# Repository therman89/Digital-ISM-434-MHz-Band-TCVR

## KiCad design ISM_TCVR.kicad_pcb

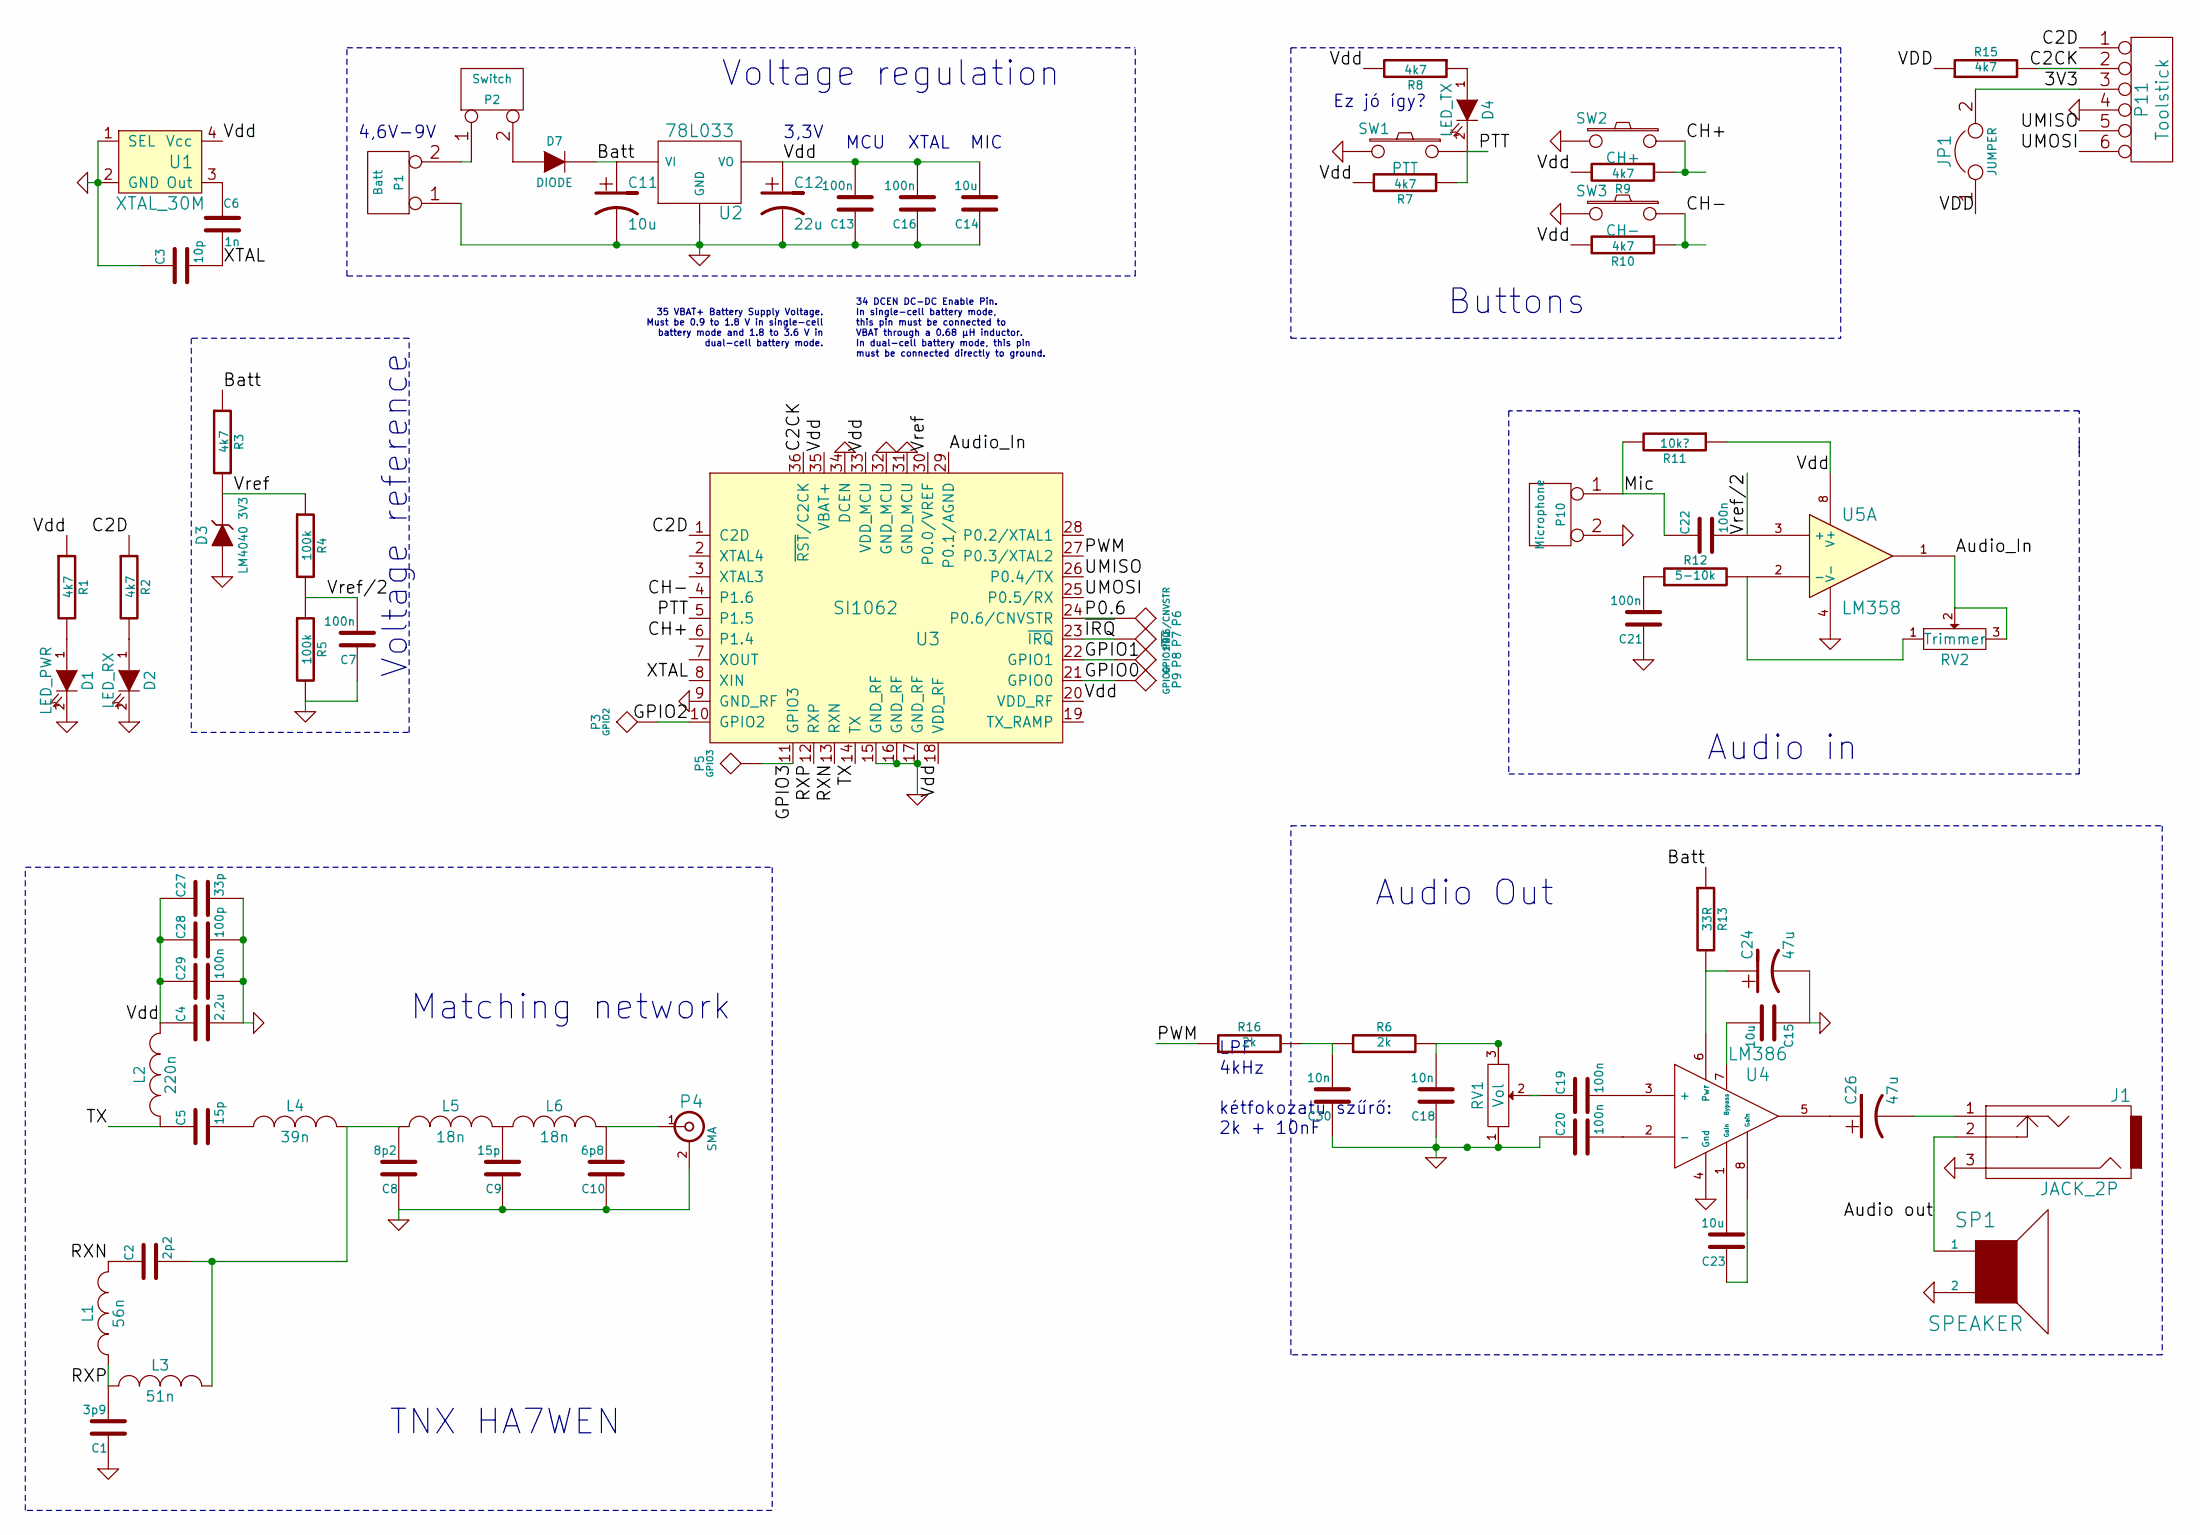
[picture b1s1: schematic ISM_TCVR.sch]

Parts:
C1: 3p9
C2: 2p2
C3: 10p
C4: 2,2u
C5, C9: 15p
C6: 1n
C7, C13, C16, C19, C20, C21, C22, C29: 100n
C8: 8p2
C10: 6p8
C11, C14, C15, C23: 10u
C12: 22u
C18, C30: 10n
C24, C26: 47u
C27: 33p
C28: 100p
D1: LED_PWR
D2: LED_RX
D3: LM4040 3V3
D4: LED_TX
D7: DIODE
J1: JACK_2P
JP1: JUMPER
L1: 56n
L2: 220n
L3: 51n
L4: 39n
L5, L6: 18n
P1: Batt
P2: Switch
P3: GPIO2
P4: SMA
P5: GPIO3
P6: P0.6/CNVSTR
P7: ~IRQ
P8: GPIO1
P9: GPIO0
P10: Microphone
P11: Toolstick
R1, R2, R3, R7, R8, R9, R10, R15: 4k7
R4, R5: 100k
R6, R16: 2k
R11: 10k?
R12: 5-10k
R13: 33R
RV1: Vol
RV2: Trimmer
SP1: SPEAKER
SW1: PTT
SW2: CH+
SW3: CH-
U1: XTAL_30M
U2: 78L033
U3: SI1062
U4: LM386
U5: LM358

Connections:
/3V3: JP1.2, P11.3
/Audio out: J1.2, SP1.1
/Audio_In: RV2.2, RV2.3, U3.29 (P0.1/AGND), U5.1
/Batt: C11.1, D7.2 (K), R3.1, R13.1, U2.3 (VI)
/C2CK: P11.2, R15.2, U3.36 (~RST~/C2CK)
/C2D: P11.1, R2.1, U3.1 (C2D)
/CH+: R9.1, SW2.1, U3.6 (P1.4)
/CH-: R10.1, SW3.1, U3.4 (P1.6)
/GPIO0: P9.1, U3.21 (GPIO0)
/GPIO1: P8.1, U3.22 (GPIO1)
/GPIO2: P3.1, U3.10 (GPIO2)
/GPIO3: P5.1, U3.11 (GPIO3)
/Mic: C22.1, P10.1, R11.2
/P0.6: P6.1, U3.24 (P0.6/CNVSTR)
/PTT: D4.2 (K), R7.1, SW1.1, U3.5 (P1.5)
/PWM: R16.1, U3.27 (P0.3/XTAL2)
/RXN: C2.1, L1.2, U3.13 (RXN)
/RXP: C1.2, L1.1, L3.1, U3.12 (RXP)
/TX: C5.1, L2.1, U3.14 (TX)
/UMISO: P11.5, U3.26 (P0.4/TX)
/UMOSI: P11.6, U3.25 (P0.5/RX)
/VDD: C4.1, C12.1, C13.2, C14.2, C16.2, C27.1, C28.1, C29.1, JP1.1, L2.2, R1.1, R7.2, R8.2, R9.2, R10.2, R11.1, R15.1, U1.4 (Vcc), U2.2 (VO), U3.18 (VDD_RF), U3.20 (VDD_RF), U3.33 (VDD_MCU), U3.35 (VBAT+), U5.8 (V+)
/Vref: D3.1 (K), R3.2, R4.1, U3.30 (P0.0/VREF)
/Vref/2: C7.2, C22.2, R4.2, R5.1, U5.3 (+)
/XTAL: C3.2, C6.2, U3.8 (XIN)
/~IRQ: P7.1, U3.23 (~IRQ)
GND: C1.1, C3.1, C4.2, C7.1, C8.1, C9.1, C10.1, C11.2, C12.2, C13.1, C14.1, C15.1, C16.1, C18.1, C20.1, C21.1, C24.2, C27.2, C28.2, C29.2, C30.1, D1.2 (K), D2.2 (K), D3.2 (A), J1.3, P1.1, P4.2 (Ext), P10.2 (PM), P11.4, R5.2, RV1.1, SP1.2, SW1.2, SW2.2, SW3.2, U1.1 (SEL), U1.2 (GND), U2.1 (GND), U3.9 (GND_RF), U3.15 (GND_RF), U3.16 (GND_RF), U3.17 (GND_RF), U3.31 (GND_MCU), U3.32 (GND_MCU), U3.34 (DCEN), U4.4 (Gnd), U5.4 (V-)
unnamed: C23.1, U4.8 (Gain)
unnamed: C18.2, R6.2, RV1.3
unnamed: C26.2, J1.1
unnamed: C2.2, C8.2, L3.2, L4.2, L5.1
unnamed: C10.2, L6.2, P4.1 (In)
unnamed: D7.1 (A), P2.2 (PM)
unnamed: P1.2 (PM), P2.1
unnamed: C21.2, R12.1
unnamed: C15.2, U4.7 (Bypass)
unnamed: C6.1, U1.3 (Out)
unnamed: C30.2, R6.1, R16.2
unnamed: C24.1, R13.2, U4.6 (Pwr)
unnamed: C19.1, RV1.2
unnamed: R12.2, RV2.1, U5.2 (-)
unnamed: C23.2, U4.1 (Gain)
unnamed: C26.1, U4.5
unnamed: C19.2, U4.3 (+)
unnamed: C20.2, U4.2 (-)
unnamed: C9.2, L5.2, L6.1
unnamed: C5.2, L4.1
unnamed: D1.1 (A), R1.2
unnamed: D2.1 (A), R2.2
unnamed: D4.1 (A), R8.1

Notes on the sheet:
Matching network
LPF 4kHz kétfokozatú szűrő: 2k + 10nF
3,3V
MCU
MIC
4,6V-9V
34 DCEN DC-DC Enable Pin. In single-cell battery mode, this pin must be connected to VBAT through a 0.68 μH inductor. In dual-cell battery mode, this pin must be connected directly to ground.
35 VBAT+ Battery Supply Voltage. Must be 0.9 to 1.8 V in single-cell battery mode and 1.8 to 3.6 V in dual-cell battery mode.
Audio in
Audio Out
Voltage regulation
TNX HA7WEN
Voltage reference
XTAL
Buttons
Ez jó így?

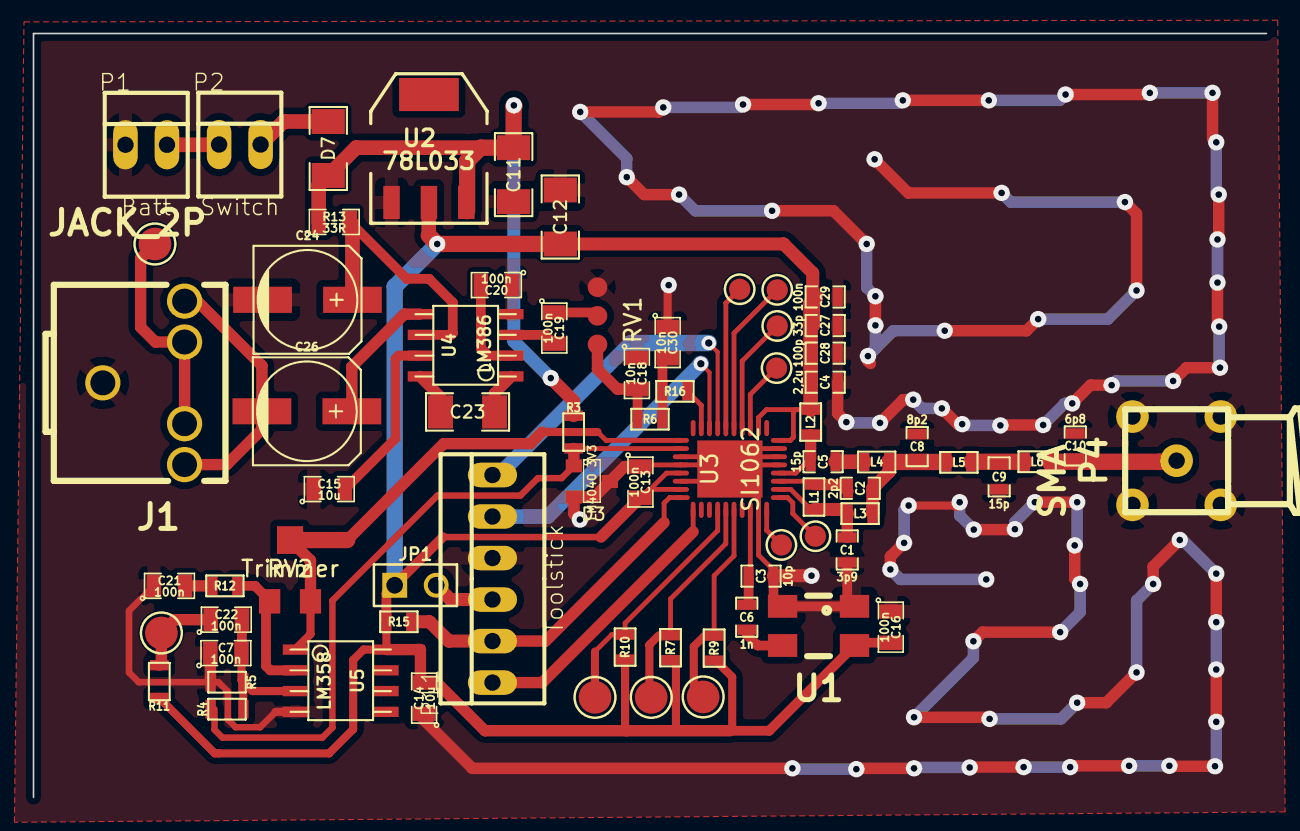
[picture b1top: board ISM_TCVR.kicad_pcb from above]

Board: 2 copper layers, 75.4 x 46.7 mm, 72 parts (0 on the bottom side), 47 nets.

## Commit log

2015-02-08 :boom::camel: Added .gitattributes & .gitignore files
2015-02-08 My first commit
    It creates the KiCad project file
2015-02-12 PCB routed
    First version of the PCB is ready. LEDs not placed yet. Hungarian
    comments
